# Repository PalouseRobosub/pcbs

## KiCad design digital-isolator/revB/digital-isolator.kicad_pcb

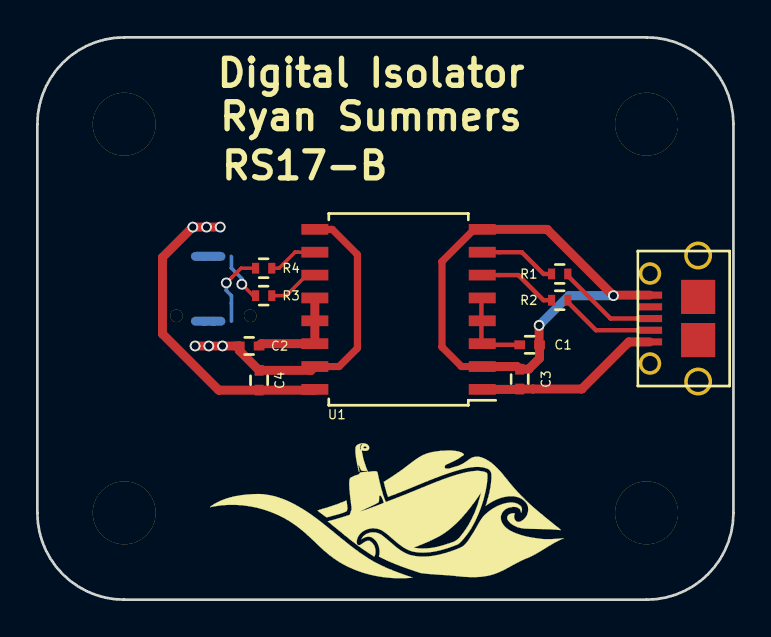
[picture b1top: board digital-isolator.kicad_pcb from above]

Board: 2 copper layers, 38.7 x 31.2 mm, 15 parts (1 on the bottom side), 14 nets.

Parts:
C1, C2, C3, C4: 100nF; C_0402
P1: USB_OTG; USB-Micro-B-TH
P2: Mezzanine-Receptacle; 3mm-10pos-outer-shroud
P3, P4, P5, P6: CONN_01X01; 3mm-spacer
R1, R2, R3, R4: 24/1%; R_0402
U1: ADUM3160; SOIC-16W_7.5x10.3mm_Pitch1.27mm

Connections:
/Vbus1: C3.1, P1.1, U1.1
/Vbus2: C4.1, P2.1, P2.3, P2.5, P2.7, U1.16
/Vdd1: C1.1, U1.3, U1.4, U1.5
/Vdd2: C2.1, U1.12, U1.13, U1.14
/usb1+: P1.3, R1.2
/usb1-: P1.2, R2.2
/usb2+: P2.10, R4.1
/usb2-: P2.9, R3.1
GND: C1.2, C3.2, P1.5, U1.2, U1.8
GNDPWR: C2.2, C4.2, P2.2, P2.4, P2.6, P2.8, U1.9, U1.15
unnamed: R1.1, U1.7
unnamed: R2.1, U1.6
unnamed: R3.2, U1.11
unnamed: R4.2, U1.10

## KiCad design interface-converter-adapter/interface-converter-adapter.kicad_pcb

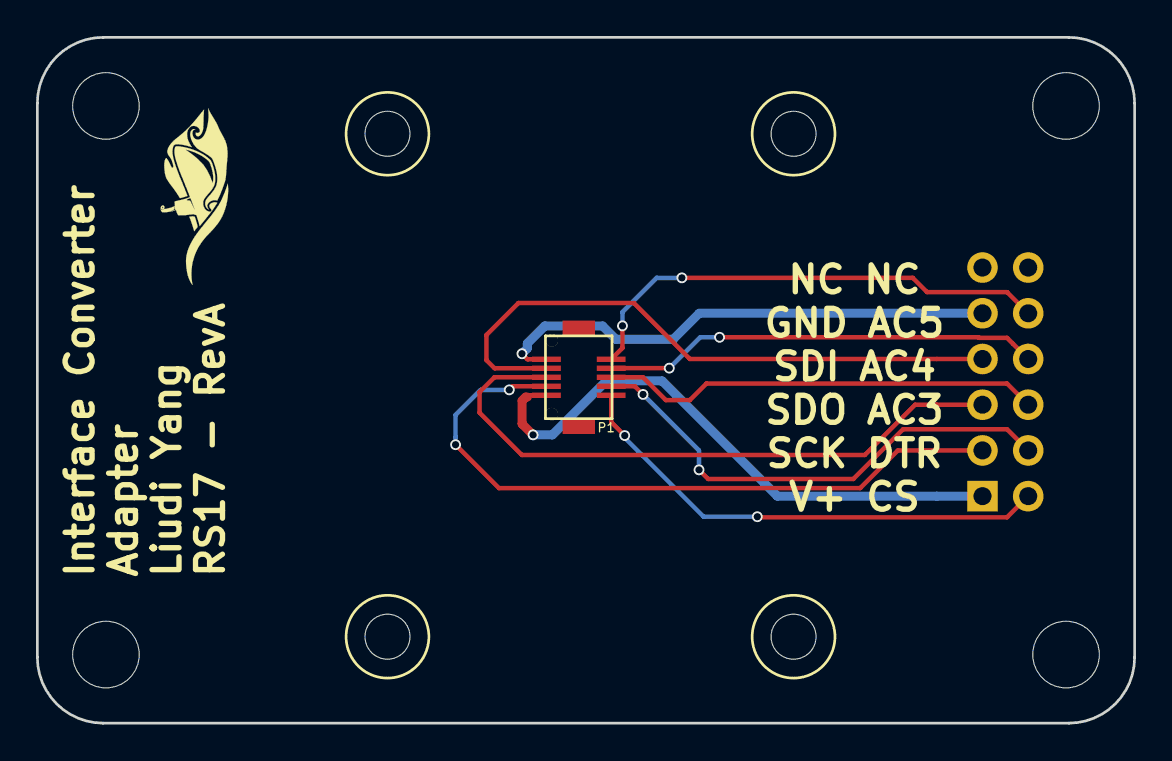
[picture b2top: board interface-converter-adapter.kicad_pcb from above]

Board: 2 copper layers, 61.0 x 38.1 mm, 6 parts (1 on the bottom side), 10 nets.

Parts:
P1: Mezzanine-Header; 3mm-10pos-receptacle
P2: CONN_02X06; Pin_Header_Straight_2x06_Pitch2.54mm
U1, U2, U3, U4: 3mm-support

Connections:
/AC3: P1.6, P2.6
/AC4: P1.8, P2.8
/AC5: P1.10, P2.10
/CS: P1.2, P2.2
/DTR: P1.4, P2.4
/GND: P1.9, P2.9
/RX/SDO: P1.5, P2.5
/SDI: P1.7, P2.7
/TX/SCK: P1.3, P2.3
/Vbus: P1.1, P2.1

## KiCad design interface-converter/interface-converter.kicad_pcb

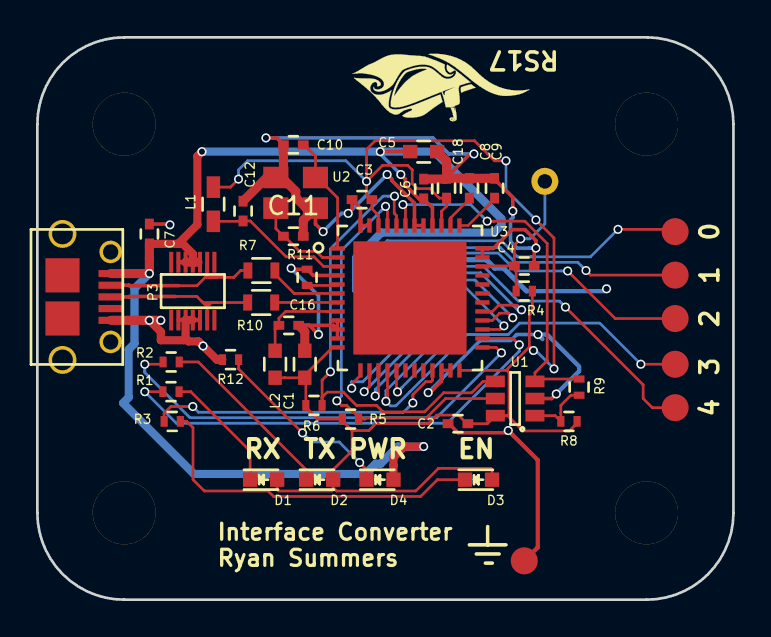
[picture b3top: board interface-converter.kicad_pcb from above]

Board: 2 copper layers, 38.7 x 31.2 mm, 49 parts (1 on the bottom side), 34 nets.

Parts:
C1, C5: 4.7u; C_0603
C2, C3, C6, C8, C9, C12, C16, C18: 100n; C_0402
C4, C7: 10n; C_0402
C10, C11: 20p; C_0402
D1: TX; LED_0603
D2: RX; LED_0603
D3: ON; LED_0603
D4: LED; LED_0603
L1: 1u; C_0603_HandSoldering
L2: 1u; C_0603
P1: USB_OTG; USB-Micro-B-TH
P2: CONN_02X05; DF40C-10DS-Receptacle
P3: CONN_02X05; DF40C-10DP-Header
P4, P5, P6, P7: CONN_01X01; 1.5mm-spacer
P8, P9, P10, P11, P12, P13: TST; Measurement_Point_Round-SMD-Pad_Small
R1: 5; R_0402
R2, R3: 65; R_0402
R4, R5, R6, R8: 10k; R_0402
R7, R10: 0; R_0603
R9: 2k; R_0402
R11: 12k/1%; R_0402
R12: 150; R_0402
U1: 93LCxxB-6; SOT-23-6
U2: ABM8G-12M; DFN-4
U3: FT232H; QFN_48-8x8
W1: TEST_1P; Measurement_Point_Round-TH_Small

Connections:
+3V3: C1.1, C2.1, C3.1, C18.1, D1.2, D2.2, D3.2, L1.1, L2.1, R4.2, R5.1, R6.1, R8.1, U1.6, U3.12, U3.24, U3.39, U3.46
/AC0: R3.2, U3.21
/AC1: R2.2, U3.25
/AC2: R1.2, U3.26
/AC3: P2.6, U3.27
/AC4: P2.8, U3.28
/AC5: P2.10, U3.29
/AD0: P2.3, P12.1, U3.13
/AD1: P2.5, P11.1, U3.14
/AD2: P2.7, P10.1, U3.15
/AD3: P2.2, P9.1, U3.16
/AD4: P2.4, P8.1, U3.17
/USB+: P1.3, P3.10, R10.2
/USB-: P1.2, P3.9, R7.2
/VCCA: C9.1, U3.37
/Vbus: C5.1, C6.1, C7.1, D4.2, P1.1, P2.1, P3.1, P3.3, P3.5, P3.7, U3.40
/Vcore: C8.1, U3.38
/Vphy: C12.1, L1.2, U3.3
/Vpll: C16.1, L2.2, U3.8
/usb_f+: R10.1, U3.7
/usb_f-: R7.1, U3.6
GND: C1.2, C2.2, C3.2, C4.2, C5.2, C6.2, C7.2, C8.2, C9.2, C10.2, C11.2, C12.2, C16.2, C18.2, P1.5, P2.9, P3.2, P3.4, P3.6, P3.8, P13.1, R11.2, R12.2, U1.2, U2.2, U2.4, U3.4, U3.9, U3.10, U3.11, U3.22, U3.23, U3.35, U3.36, U3.41, U3.42, U3.47, U3.48
unnamed: C4.1, R4.1, U3.34, W1.1
unnamed: C10.1, U2.1, U3.1
unnamed: C11.1, U2.3, U3.2
unnamed: D1.1, R1.1
unnamed: D2.1, R2.1
unnamed: D3.1, R3.1
unnamed: D4.1, R12.1
unnamed: R5.2, U1.5, U3.45
unnamed: R6.2, U1.4, U3.44
unnamed: R8.2, R9.2, U1.1
unnamed: R9.1, U1.3, U3.43
unnamed: R11.1, U3.5

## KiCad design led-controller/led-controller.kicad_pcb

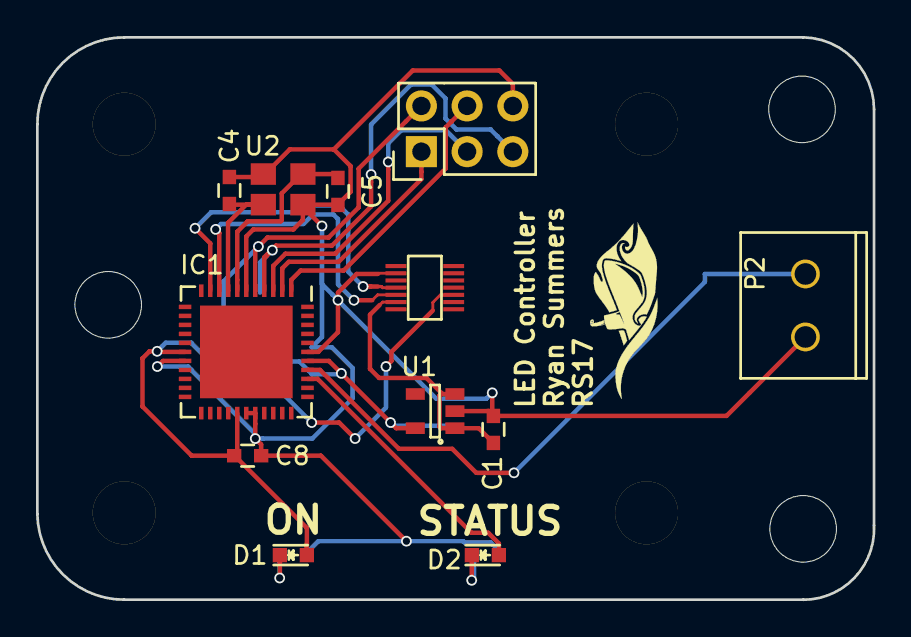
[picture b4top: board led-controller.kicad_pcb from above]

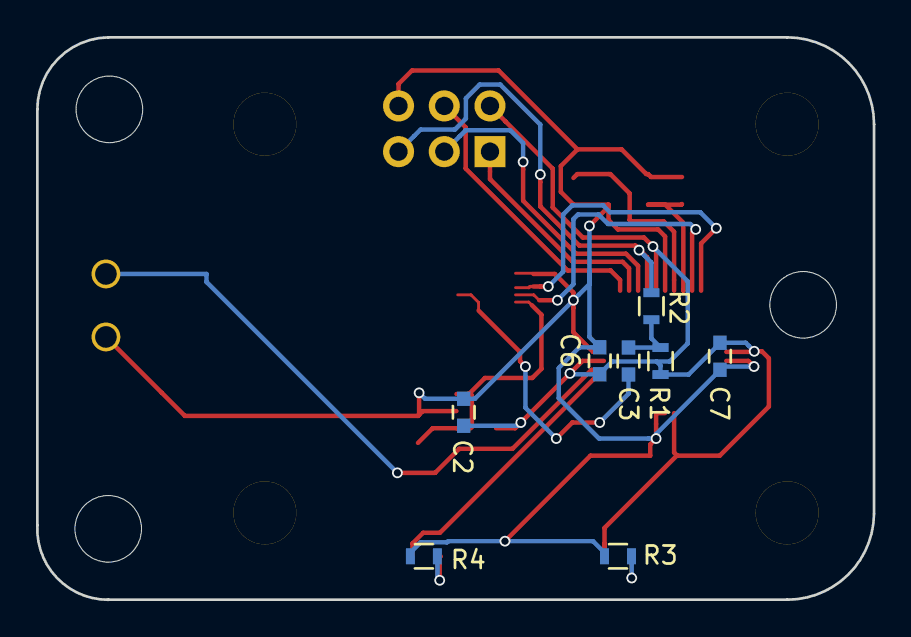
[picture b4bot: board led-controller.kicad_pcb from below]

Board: 2 copper layers, 46.5 x 31.2 mm, 24 parts (8 on the bottom side), 17 nets.

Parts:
C1: 1uF; C_0603
C2: 2.2uF; C_0603
C3: 100nF; C_0603
C4, C5: 18p; C_0603
C6, C7: 100n; C_0603
C8: 4.7u; C_0603
D1, D2: LED; LED_0603
IC1: ATMEGA1284P-M; QFN-44-1EP_7x7mm_Pitch0.5mm
P1: Mezzanine-Header; DF40C-10DP-Header
P2: Conn; Screw-Terminal-2-3.5mm
P3, P4, P5, P6: Spacer; 1.5mm-spacer
P7: CONN_02X03; Pin_Header_Straight_2x03
R1: 10k; R_0603
R2: 1k; R_0603
R3, R4: 65; R_0603
U1: TLV70012DDC; SOT-23-5
U2: TSX-3225; DFN-4

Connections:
+3V3: C2.1, C6.1, C7.1, C8.1, D1.2, IC1.5, IC1.17, IC1.27, IC1.38, P7.2, R1.1, U1.5
+5V: C1.1, P1.1, U1.1, U1.3
/DTR: C3.2, P1.4
/RX_CPU: IC1.10, P1.5
/Sheet580A8768/DBG_LED: D2.2, IC1.36
/Sheet580A8768/MISO: IC1.2, P7.1
/Sheet580A8768/MOSI: IC1.1, P7.4
/Sheet580A8768/SCK: IC1.3, P7.3
/Sheet580A8768/~RST: IC1.4, P7.5, R2.1
/TX_CPU: IC1.9, P1.3
/signal: IC1.37, P2.1
GND: C1.2, C2.2, C4.2, C5.2, C6.2, C7.2, C8.2, IC1.6, IC1.18, IC1.28, IC1.29, IC1.39, P1.9, P2.2, P7.6, R3.2, R4.2, U1.2, U2.2, U2.4
unnamed: C3.1, R1.2, R2.2
unnamed: C4.1, IC1.8, U2.3
unnamed: C5.1, IC1.7, U2.1
unnamed: D1.1, R3.1
unnamed: D2.1, R4.1
